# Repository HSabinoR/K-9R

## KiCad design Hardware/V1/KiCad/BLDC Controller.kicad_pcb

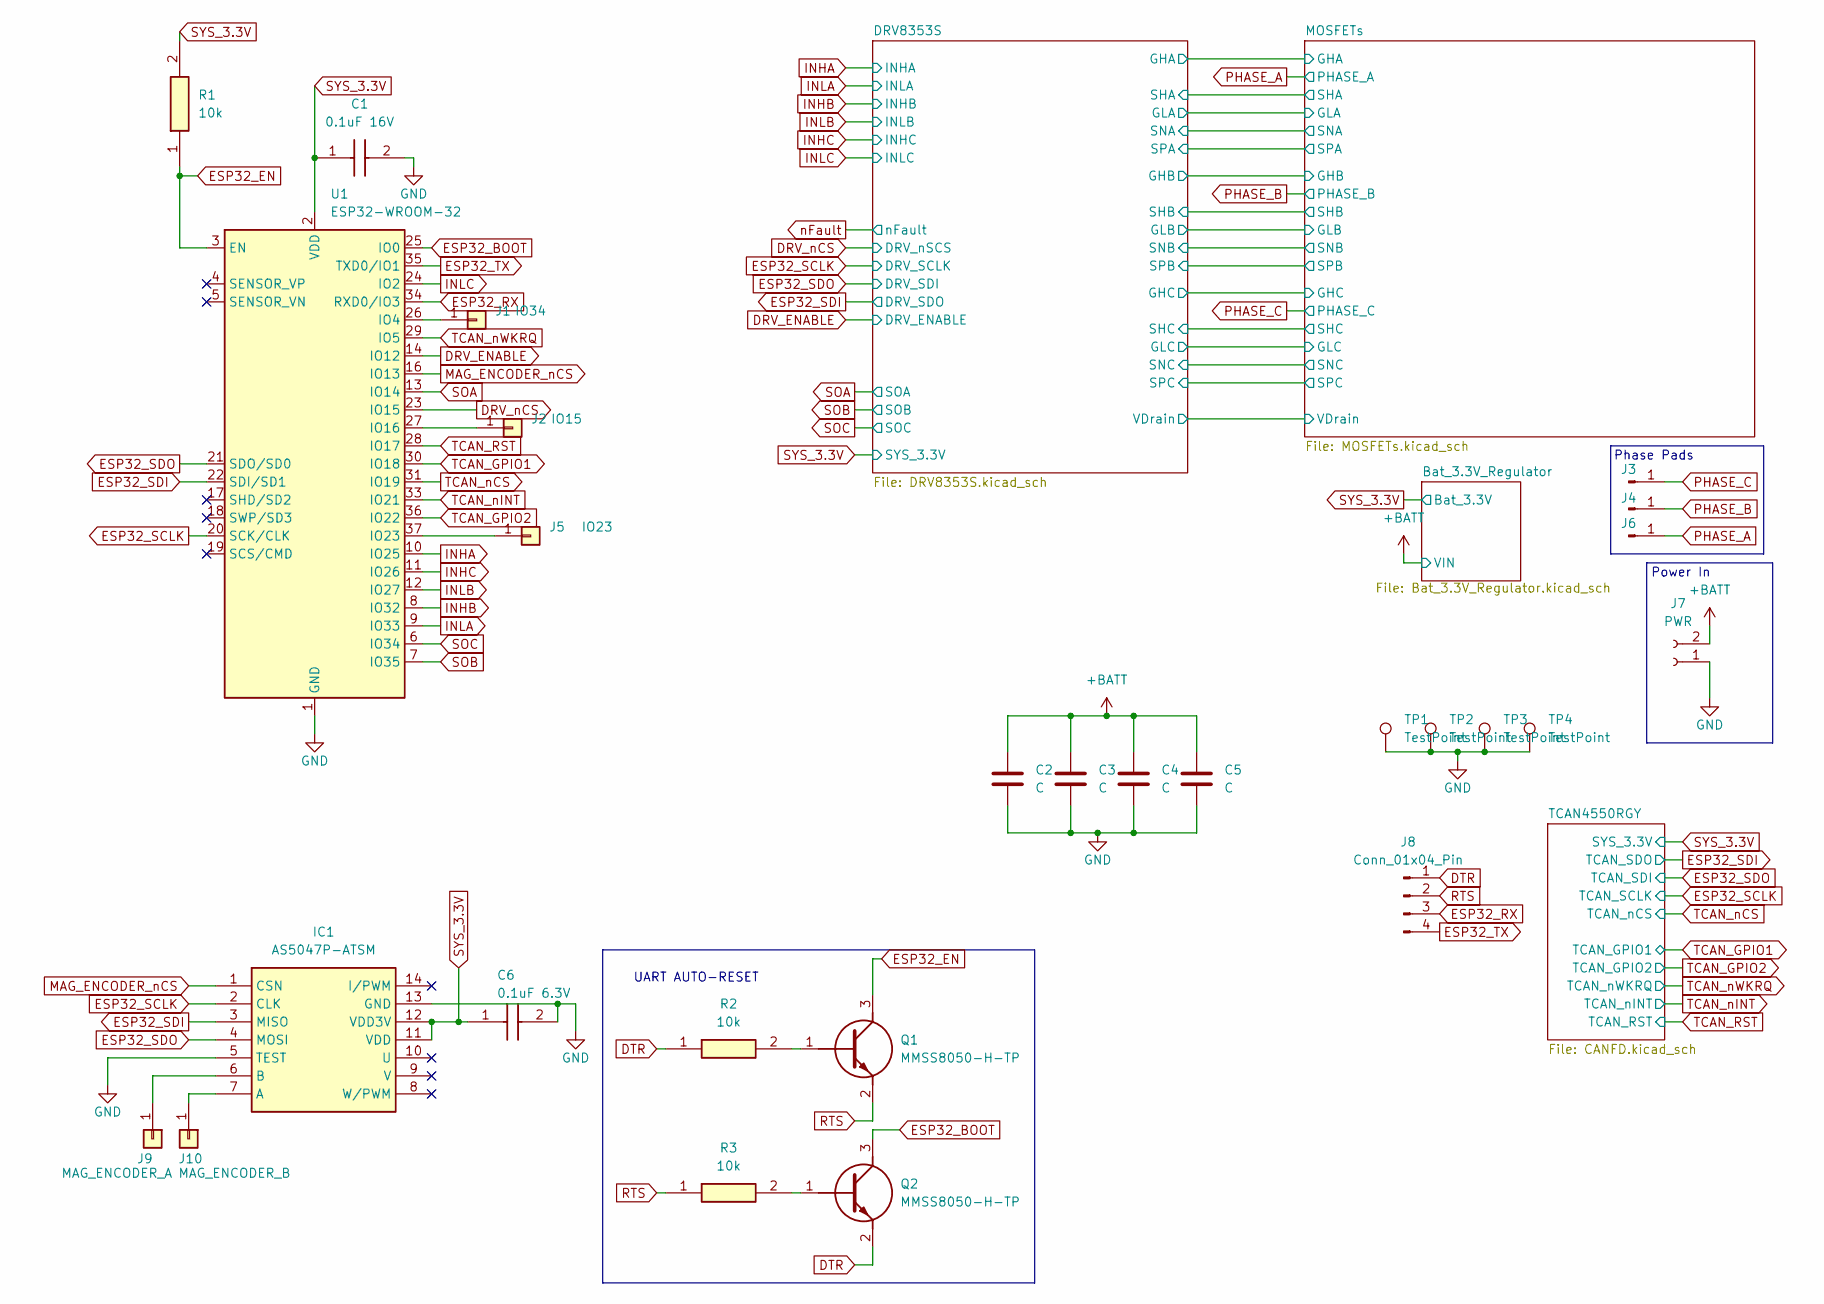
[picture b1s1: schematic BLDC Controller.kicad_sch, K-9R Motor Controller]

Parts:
C1: 0.1uF 16V; CAPC1608X90N; Mouser Part Number 581-0603YC104K4T4A
C2, C3, C4, C5: C; C_0805_2012Metric_Pad1.18x1.45mm_HandSolder
C6: 0.1uF 6.3V; CAPC2012X140N; Mouser Part Number 581-08056D104KAT2A
IC1: AS5047P-ATSM; SOP65P640X120-14N; Mouser Part Number 985-AS5047P-ATSM
J1: IO34; SolderWirePad_1x01_SMD_1x2mm
J2: IO15; SolderWirePad_1x01_SMD_1x2mm
J3, J4, J6: Conn_01x01_Pin; SolderWire-6sqmm_1x01_D3.5mm_OD7mm
J5: IO23; SolderWirePad_1x01_SMD_1x2mm
J7: PWR; AMASS_XT30U-M_1x02_P5.0mm_Vertical
J8: Conn_01x04_Pin; PinHeader_1x04_P2.54mm_Vertical
J9: MAG_ENCODER_A; SolderWirePad_1x01_SMD_1x2mm
J10: MAG_ENCODER_B; SolderWirePad_1x01_SMD_1x2mm
Q1, Q2: MMSS8050-H-TP; SOT-23; Mouser Part Number 833-MMSS8050-H-TP
R1, R2, R3: 10k; RESC2012X65N; Mouser Part Number 755-ESR10EZPF1002
TP1, TP2, TP3, TP4: TestPoint; TestPoint_Plated_Hole_D3.0mm
U1: ESP32-WROOM-32

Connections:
+BATT: C2.1, C3.1, C4.1, C5.1, J7.2; also elsewhere on the board
DRV_ENABLE: U1.14 (IO12); also elsewhere on the board
DRV_nCS: U1.23 (IO15); also elsewhere on the board
DTR: J8.1, Q2.2 (E), R2.1
ESP32_BOOT: Q2.3 (C), U1.25 (IO0)
ESP32_EN: Q1.3 (C), R1.1, U1.3 (EN)
ESP32_RX: J8.3, U1.34 (RXD0/IO3)
ESP32_SCLK: IC1.2 (CLK), U1.20 (SCK/CLK); also elsewhere on the board
ESP32_SDI: IC1.3 (MISO), U1.22 (SDI/SD1); also elsewhere on the board
ESP32_SDO: IC1.4 (MOSI), U1.21 (SDO/SD0); also elsewhere on the board
ESP32_TX: J8.4, U1.35 (TXD0/IO1)
GND: C1.2, C2.2, C3.2, C4.2, C5.2, C6.2, IC1.5 (TEST), IC1.13 (GND), J7.1, TP1.1, TP2.1, TP3.1, TP4.1, U1.1 (GND), U1.15 (GND), U1.38 (GND), U1.39 (GND); also elsewhere on the board
INHA: U1.10 (IO25); also elsewhere on the board
INHB: U1.8 (IO32); also elsewhere on the board
INHC: U1.11 (IO26); also elsewhere on the board
INLA: U1.9 (IO33); also elsewhere on the board
INLB: U1.12 (IO27); also elsewhere on the board
INLC: U1.24 (IO2); also elsewhere on the board
MAG_ENCODER_nCS: IC1.1 (CSN), U1.16 (IO13)
unnamed: IC1.7 (A), J10.1
unnamed: IC1.6 (B), J9.1
unnamed: J1.1, U1.26 (IO4)
unnamed: J2.1, U1.27 (IO16)
unnamed: J5.1, U1.37 (IO23)
unnamed: Q1.1 (B), R2.2
unnamed: Q2.1 (B), R3.2
PHASE_A: J6.1; also elsewhere on the board
PHASE_B: J4.1; also elsewhere on the board
PHASE_C: J3.1; also elsewhere on the board
RTS: J8.2, Q1.2 (E), R3.1
SOA: U1.13 (IO14); also elsewhere on the board
SOB: U1.7 (IO35); also elsewhere on the board
SOC: U1.6 (IO34); also elsewhere on the board
SYS_3.3V: C1.1, C6.1, IC1.11 (VDD), IC1.12 (VDD3V), R1.2, U1.2 (VDD); also elsewhere on the board
TCAN_GPIO1: U1.30 (IO18); also elsewhere on the board
TCAN_GPIO2: U1.36 (IO22); also elsewhere on the board
TCAN_RST: U1.28 (IO17); also elsewhere on the board
TCAN_nCS: U1.31 (IO19); also elsewhere on the board
TCAN_nINT: U1.33 (IO21); also elsewhere on the board
TCAN_nWKRQ: U1.29 (IO5); also elsewhere on the board

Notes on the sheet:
Power In
UART AUTO-RESET
Phase Pads

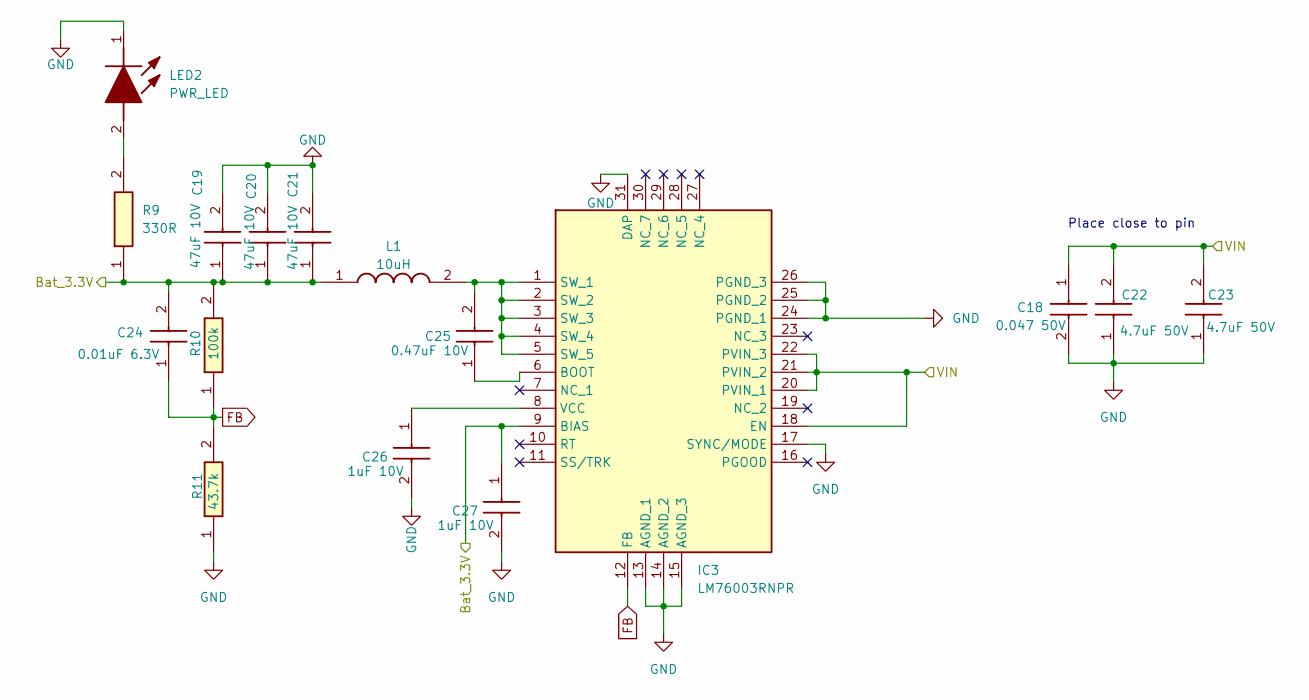
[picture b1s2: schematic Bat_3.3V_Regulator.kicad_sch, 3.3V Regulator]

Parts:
C18: 0.047 50V; CAPC1608X90N; Mouser Part Number 603-AC603KPX7R9BB473
C19, C20, C21: 47uF 10V; CAPC2012X145N; Mouser Part Number 81-GRM21BR61A476ME5L
C22, C23: 4.7uF 50V; CAPC3216X229N; Mouser Part Number 581-12065D475MAT2A
C24: 0.01uF 6.3V; C0603; Mouser Part Number 80-C0603C103K9R
C25: 0.47uF 10V; CAPC1608X90N; Manufacturer_Part_Number GRM188R71A474JA61J
C26, C27: 1uF 10V; CAPC1608X90N; Mouser Part Number 963-LMK107B7105KA-T
IC3: LM76003RNPR; Mouser Part Number 595-LM76003RNPR
L1: 10uH; INDPM6965X240N; Mouser Part Number 70-IHLP2525BDER100M1
LED2: PWR_LED; KREELP4122Q1S136A8J8020R18; Mouser Part Number 720-P412Q1S136A8J802
R9: 330R; RESC2012X55N; Mouser Part Number 594-MCU08050C3300FP5
R10: 100k; RESC2012X50N; Mouser Part Number 71-CRCW0805J-100K-E3
R11: 43.7k; RESC1005X40N; Mouser Part Number 71-TNPW040243K7BEED

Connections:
+BATT: C18.1, C22.2, C23.2, IC3.18 (EN), IC3.20 (PVIN_1), IC3.21 (PVIN_2), IC3.22 (PVIN_3); also elsewhere on the board
FB: C24.1, IC3.12 (FB), R10.1, R11.2
GND: C18.2, C19.2, C20.2, C21.2, C22.1, C23.1, C26.2, C27.2, IC3.13 (AGND_1), IC3.14 (AGND_2), IC3.15 (AGND_3), IC3.17 (SYNC/MODE), IC3.24 (PGND_1), IC3.25 (PGND_2), IC3.26 (PGND_3), IC3.31 (DAP), LED2.1 (K), R11.1; also elsewhere on the board
unnamed: C25.1, IC3.6 (BOOT)
unnamed: C25.2, IC3.1 (SW_1), IC3.2 (SW_2), IC3.3 (SW_3), IC3.4 (SW_4), IC3.5 (SW_5), L1.2
unnamed: C26.1, IC3.8 (VCC)
unnamed: LED2.2 (A), R9.2
SYS_3.3V: C19.1, C20.1, C21.1, C24.2, C27.1, IC3.9 (BIAS), L1.1, R9.1, R10.2; also elsewhere on the board

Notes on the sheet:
Place close to pin

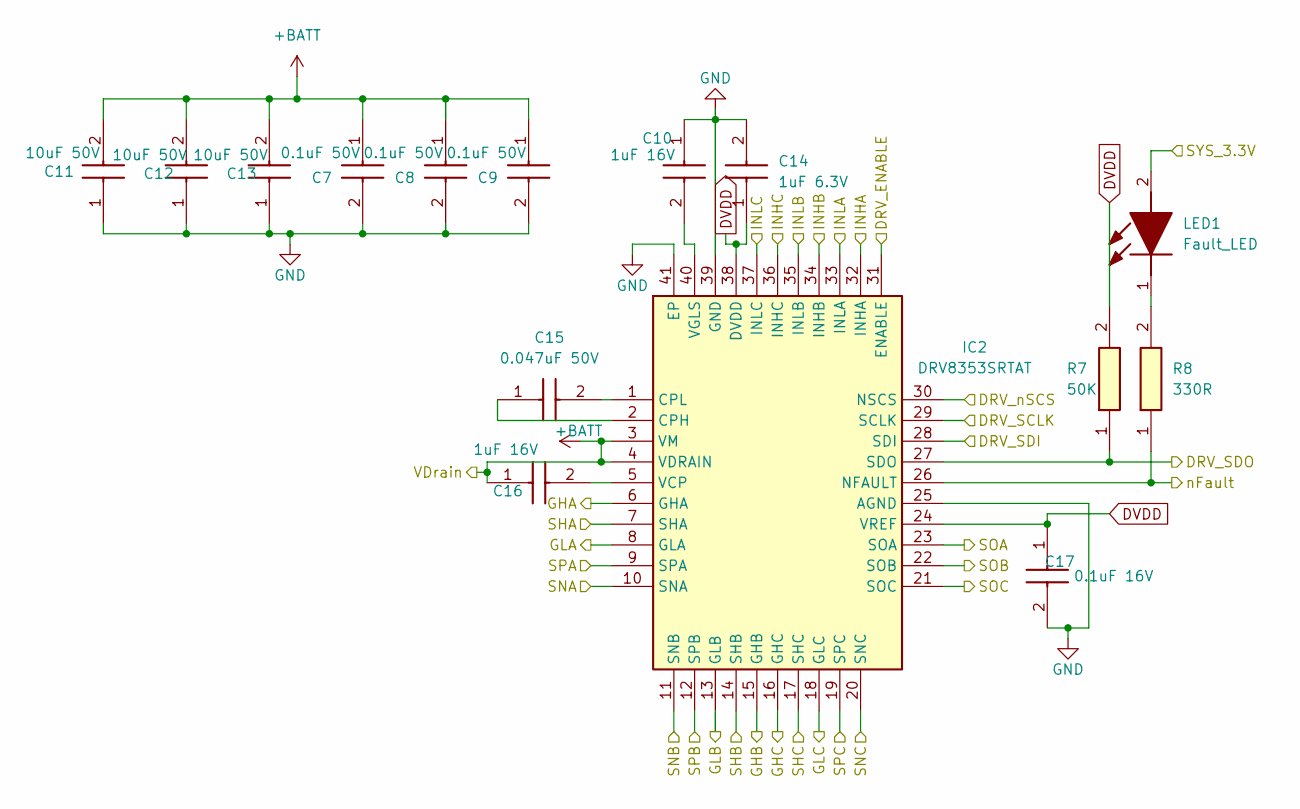
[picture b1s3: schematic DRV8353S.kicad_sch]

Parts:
C7, C8, C9: 0.1uF 50V; CAPC2012X94N; Mouser Part Number 581-KAM21BR71H104JT
C10, C16: 1uF 16V; CAPC2012X145N; Mouser Part Number 581-KGM21AR71C105JU
C11, C12, C13: 10uF 50V; CAPC3225X270N; Mouser Part Number 963-UMK325C7106KM-T
C14: 1uF 6.3V; CAPC1005X55N; Mouser Part Number 963-JMK105BJ105KV-F
C15: 0.047uF 50V; CAPC1608X90N; Mouser Part Number 603-AC603KPX7R9BB473
C17: 0.1uF 16V; CAPC1608X90N; Mouser Part Number 581-0603YC104K4T4A
IC2: DRV8353SRTAT; QFN50P600X600X80-41N-D; Mouser Part Number 595-DRV8353SRTAT
LED1: Fault_LED; KREELP4122Q1S136A8J8020R18; Mouser Part Number 720-P412Q1S136A8J802
R7: 50K; RESC1608X55N; Mouser Part Number 603-RT0603BRD0750KL
R8: 330R; RESC2012X55N; Mouser Part Number 594-MCU08050C3300FP5

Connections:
+BATT: C7.1, C8.1, C9.1, C11.2, C12.2, C13.2, C16.1, IC2.3 (VM), IC2.4 (VDRAIN); also elsewhere on the board
/DRV8353S/GHA: IC2.6 (GHA); also elsewhere on the board
/DRV8353S/GHB: IC2.15 (GHB); also elsewhere on the board
/DRV8353S/GHC: IC2.16 (GHC); also elsewhere on the board
/DRV8353S/GLA: IC2.8 (GLA); also elsewhere on the board
/DRV8353S/GLB: IC2.13 (GLB); also elsewhere on the board
/DRV8353S/GLC: IC2.18 (GLC); also elsewhere on the board
/DRV8353S/SPA: IC2.9 (SPA); also elsewhere on the board
/DRV8353S/SPB: IC2.12 (SPB); also elsewhere on the board
/DRV8353S/SPC: IC2.19 (SPC); also elsewhere on the board
DRV_ENABLE: IC2.31 (ENABLE); also elsewhere on the board
DRV_nCS: IC2.30 (NSCS); also elsewhere on the board
DVDD: C14.1, C17.1, IC2.24 (VREF), IC2.38 (DVDD), R7.2
ESP32_SCLK: IC2.29 (SCLK); also elsewhere on the board
ESP32_SDI: IC2.27 (SDO), R7.1; also elsewhere on the board
ESP32_SDO: IC2.28 (SDI); also elsewhere on the board
GND: C7.2, C8.2, C9.2, C10.1, C11.1, C12.1, C13.1, C14.2, C17.2, IC2.10 (SNA), IC2.11 (SNB), IC2.20 (SNC), IC2.25 (AGND), IC2.39 (GND), IC2.41 (EP); also elsewhere on the board
INHA: IC2.32 (INHA); also elsewhere on the board
INHB: IC2.34 (INHB); also elsewhere on the board
INHC: IC2.36 (INHC); also elsewhere on the board
INLA: IC2.33 (INLA); also elsewhere on the board
INLB: IC2.35 (INLB); also elsewhere on the board
INLC: IC2.37 (INLC); also elsewhere on the board
unnamed: C15.1, IC2.2 (CPH)
unnamed: C15.2, IC2.1 (CPL)
unnamed: C16.2, IC2.5 (VCP)
unnamed: C10.2, IC2.40 (VGLS)
unnamed: LED1.1 (K), R8.2
PHASE_A: IC2.7 (SHA); also elsewhere on the board
PHASE_B: IC2.14 (SHB); also elsewhere on the board
PHASE_C: IC2.17 (SHC); also elsewhere on the board
SOA: IC2.23 (SOA); also elsewhere on the board
SOB: IC2.22 (SOB); also elsewhere on the board
SOC: IC2.21 (SOC); also elsewhere on the board
SYS_3.3V: LED1.2 (A); also elsewhere on the board
nFault: IC2.26 (NFAULT), R8.1

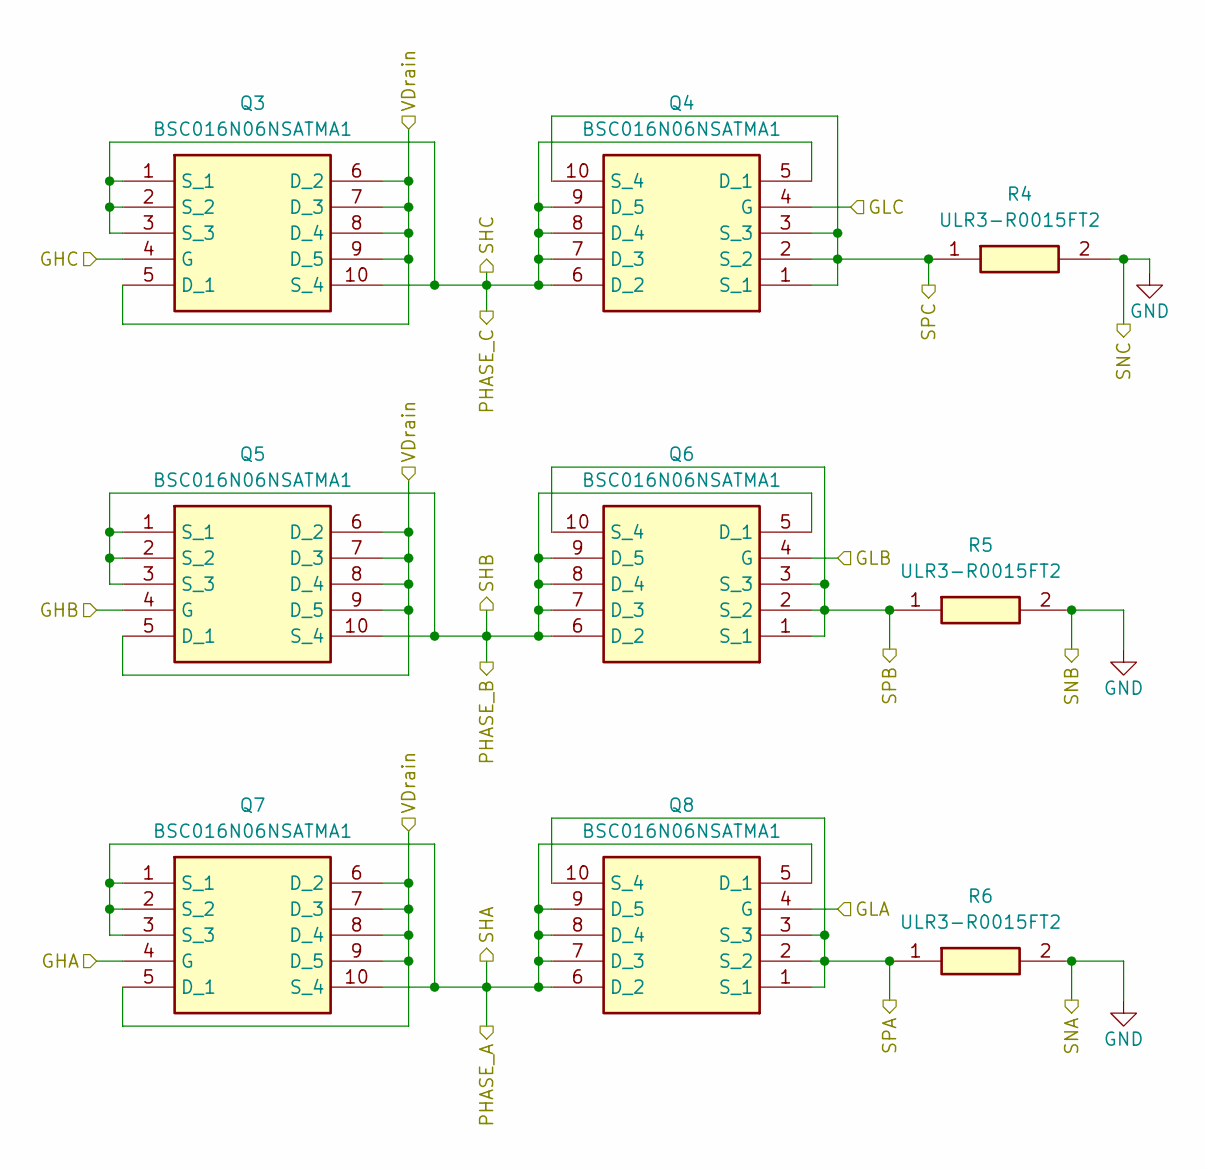
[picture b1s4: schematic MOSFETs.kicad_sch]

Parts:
Q3, Q4, Q5, Q6, Q7, Q8: BSC016N06NSATMA1; BSC016N06NS; Mouser Part Number 726-BSC016N06NSATMA1
R4, R5, R6: ULR3-R0015FT2; RESC6430X80N; Mouser Part Number 756-ULR3-R0015FT2

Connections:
+BATT: Q3.5 (D_1), Q3.6 (D_2), Q3.7 (D_3), Q3.8 (D_4), Q3.9 (D_5), Q5.5 (D_1), Q5.6 (D_2), Q5.7 (D_3), Q5.8 (D_4), Q5.9 (D_5), Q7.5 (D_1), Q7.6 (D_2), Q7.7 (D_3), Q7.8 (D_4), Q7.9 (D_5); also elsewhere on the board
/DRV8353S/GHA: Q7.4 (G); also elsewhere on the board
/DRV8353S/GHB: Q5.4 (G); also elsewhere on the board
/DRV8353S/GHC: Q3.4 (G); also elsewhere on the board
/DRV8353S/GLA: Q8.4 (G); also elsewhere on the board
/DRV8353S/GLB: Q6.4 (G); also elsewhere on the board
/DRV8353S/GLC: Q4.4 (G); also elsewhere on the board
/DRV8353S/SPA: Q8.1 (S_1), Q8.2 (S_2), Q8.3 (S_3), Q8.10 (S_4), R6.1; also elsewhere on the board
/DRV8353S/SPB: Q6.1 (S_1), Q6.2 (S_2), Q6.3 (S_3), Q6.10 (S_4), R5.1; also elsewhere on the board
/DRV8353S/SPC: Q4.1 (S_1), Q4.2 (S_2), Q4.3 (S_3), Q4.10 (S_4), R4.1; also elsewhere on the board
GND: R4.2, R5.2, R6.2; also elsewhere on the board
PHASE_A: Q7.1 (S_1), Q7.2 (S_2), Q7.3 (S_3), Q7.10 (S_4), Q8.5 (D_1), Q8.6 (D_2), Q8.7 (D_3), Q8.8 (D_4), Q8.9 (D_5); also elsewhere on the board
PHASE_B: Q5.1 (S_1), Q5.2 (S_2), Q5.3 (S_3), Q5.10 (S_4), Q6.5 (D_1), Q6.6 (D_2), Q6.7 (D_3), Q6.8 (D_4), Q6.9 (D_5); also elsewhere on the board
PHASE_C: Q3.1 (S_1), Q3.2 (S_2), Q3.3 (S_3), Q3.10 (S_4), Q4.5 (D_1), Q4.6 (D_2), Q4.7 (D_3), Q4.8 (D_4), Q4.9 (D_5); also elsewhere on the board

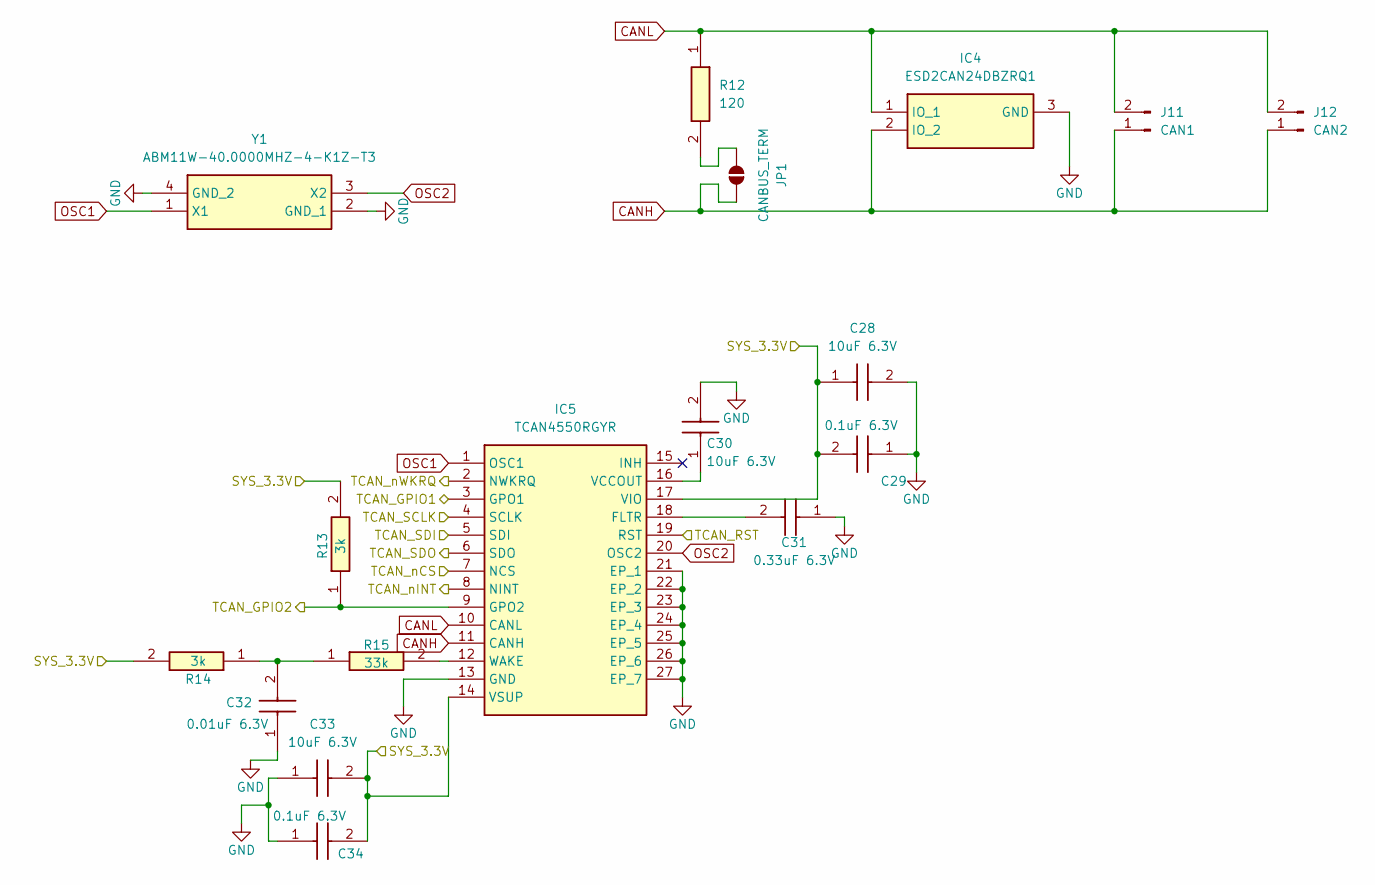
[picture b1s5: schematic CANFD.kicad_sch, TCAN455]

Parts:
C28, C30, C33: 10uF 6.3V; MBASx168; Manufacturer_Part_Number MBASJ168AB5106KTNA01
C29, C34: 0.1uF 6.3V; CAPC2012X140N; Mouser Part Number 581-08056D104KAT2A
C31: 0.33uF 6.3V; CAPC1608X90N; Mouser Part Number 81-GRM18R60J334KA01D
C32: 0.01uF 6.3V; C0603; Mouser Part Number 80-C0603C103K9R
IC4: ESD2CAN24DBZRQ1; SOT95P237X112-3N; Mouser Part Number 595-ESD2CAN24DBZRQ1
IC5: TCAN4550RGYR; TCAN4551RGYRQ1; Mouser Part Number 595-TCAN4550RGYR
J11: CAN1; JST_XH_B2B-XH-A_1x02_P2.50mm_Vertical
J12: CAN2; JST_XH_B2B-XH-A_1x02_P2.50mm_Vertical
JP1: CANBUS_TERM; SolderJumper-2_P1.3mm_Open_TrianglePad1.0x1.5mm
R12: 120; RESC2013X65N; Mouser Part Number 279-CRGS0805J120R
R13, R14: 3k; RESC2012X55N; Mouser Part Number 71-TNPW08053K00FEEA
R15: 33k; RESC2012X60N; Manufacturer_Part_Number RT0805BRD0733KL
Y1: ABM11W-40.0000MHZ-4-K1Z-T3; ABM11W300000MHZ4B1UT3; Mouser Part Number 815-11W40-4K1ZT

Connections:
CANH: IC4.2 (IO_2), IC5.11 (CANH), J11.1, J12.1, JP1.2 (B)
CANL: IC4.1 (IO_1), IC5.10 (CANL), J11.2, J12.2, R12.1
ESP32_SCLK: IC5.4 (SCLK); also elsewhere on the board
ESP32_SDI: IC5.6 (SDO); also elsewhere on the board
ESP32_SDO: IC5.5 (SDI); also elsewhere on the board
GND: C28.2, C29.1, C30.2, C31.1, C32.1, C33.1, C34.1, IC4.3 (GND), IC5.13 (GND), IC5.21 (EP_1), IC5.22 (EP_2), IC5.23 (EP_3), IC5.24 (EP_4), IC5.25 (EP_5), IC5.26 (EP_6), IC5.27 (EP_7), Y1.2 (GND_1), Y1.4 (GND_2); also elsewhere on the board
unnamed: C32.2, R14.1, R15.1
unnamed: C31.2, IC5.18 (FLTR)
unnamed: C30.1, IC5.16 (VCCOUT)
unnamed: IC5.12 (WAKE), R15.2
unnamed: JP1.1 (A), R12.2
OSC1: IC5.1 (OSC1), Y1.1 (X1)
OSC2: IC5.20 (OSC2), Y1.3 (X2)
SYS_3.3V: C28.1, C29.2, C33.2, C34.2, IC5.14 (VSUP), IC5.17 (VIO), R13.2, R14.2; also elsewhere on the board
TCAN_GPIO1: IC5.3 (GPO1); also elsewhere on the board
TCAN_GPIO2: IC5.9 (GPO2), R13.1; also elsewhere on the board
TCAN_RST: IC5.19 (RST); also elsewhere on the board
TCAN_nCS: IC5.7 (NCS); also elsewhere on the board
TCAN_nINT: IC5.8 (NINT); also elsewhere on the board
TCAN_nWKRQ: IC5.2 (NWKRQ); also elsewhere on the board

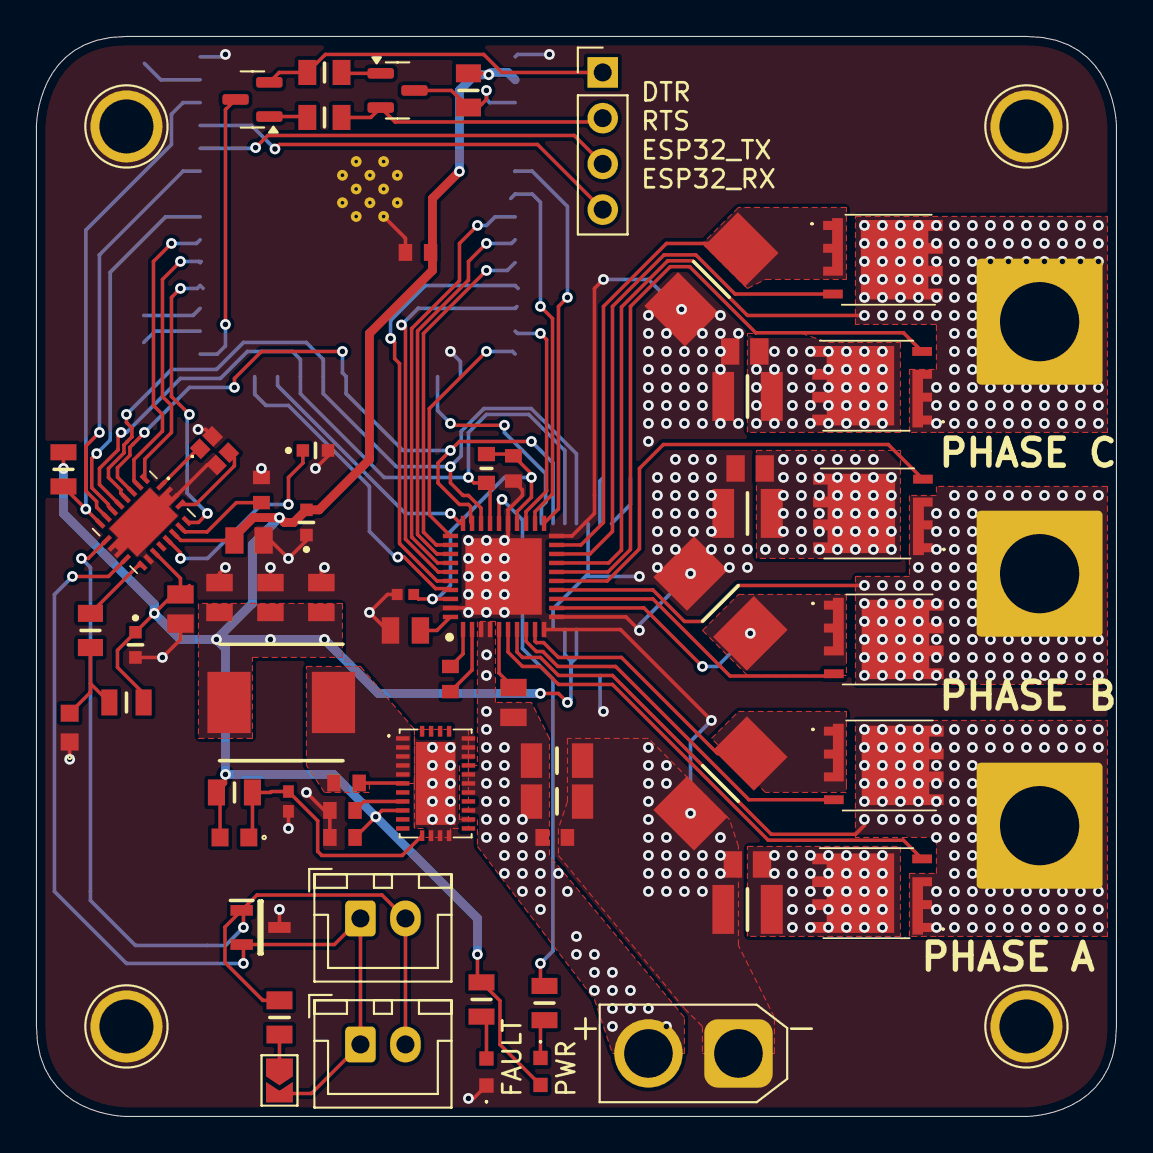
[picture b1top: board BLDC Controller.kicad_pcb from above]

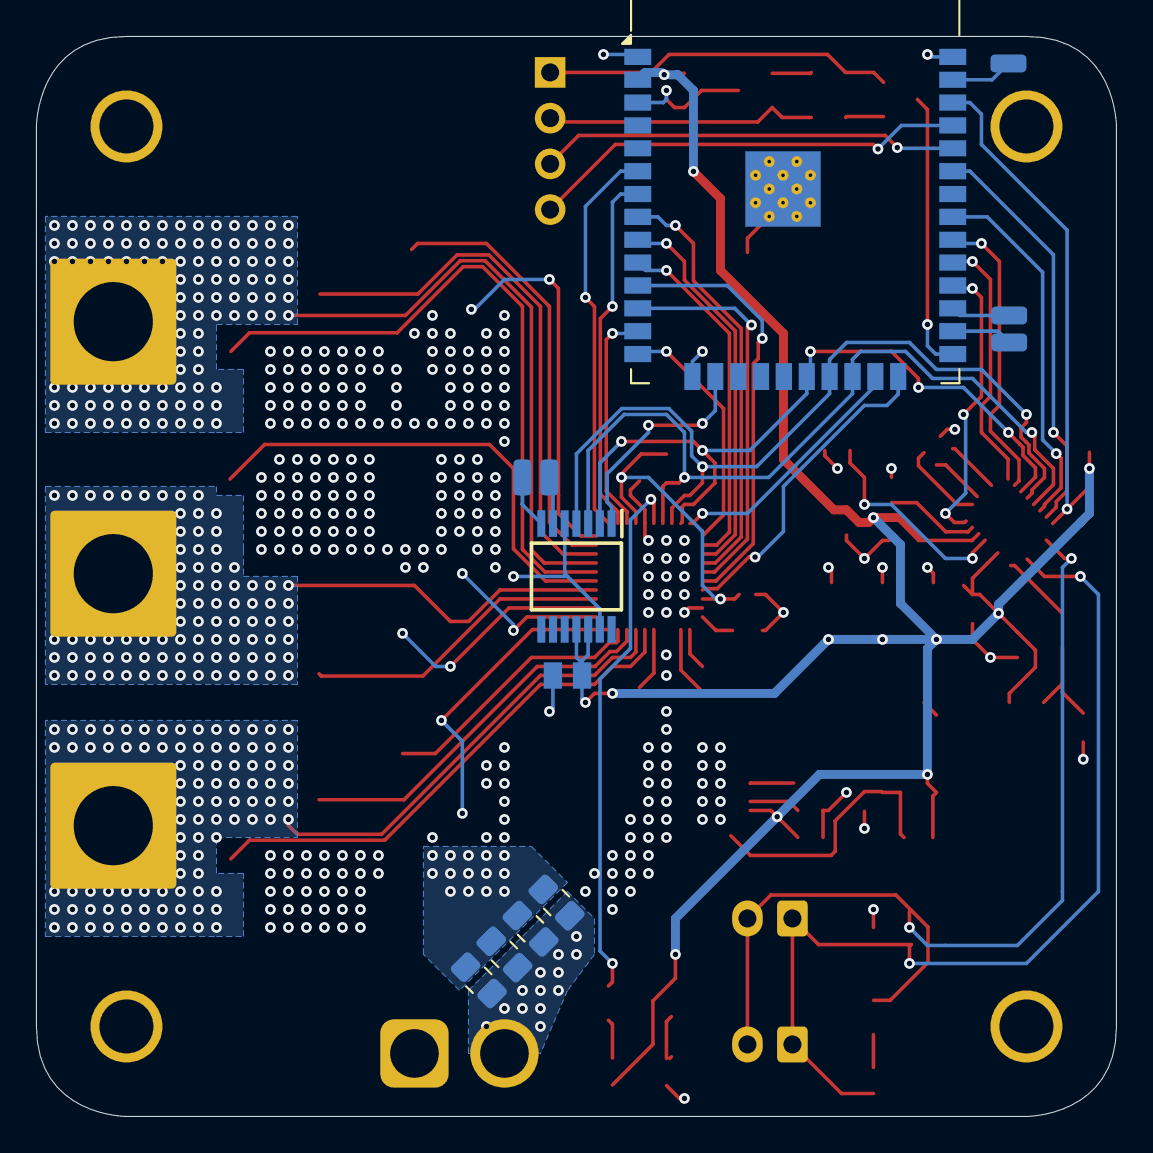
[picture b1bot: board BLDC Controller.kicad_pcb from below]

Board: 4 copper layers, 60.0 x 60.0 mm, 84 parts (12 on the bottom side), 70 nets.

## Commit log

2025-10-08 Add files via upload
    Schemtaic, 3D View, and Gerber Files
2025-10-08 Layers & BOM's
2025-10-08 Create temp
2025-10-08 Added KiCad Files
2025-10-08 Test
2025-10-08 Slight Update
2025-10-09 Register Maps of TCAN4550
2025-10-09 Default Power Up Configuration
2025-10-09 Test Code
2025-10-09 TCAN455 DataSheet
2025-10-10 Created a PlatformIO Project
2025-11-18 Backup and Reorganise
